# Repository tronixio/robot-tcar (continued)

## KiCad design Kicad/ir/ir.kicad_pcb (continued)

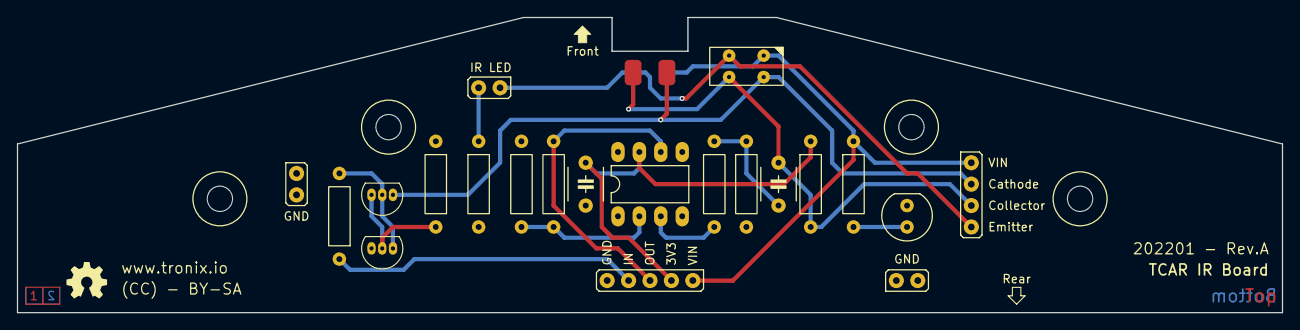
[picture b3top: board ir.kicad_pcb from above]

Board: 2 copper layers, 150.0 x 35.0 mm, 26 parts (1 on the bottom side), 15 nets.

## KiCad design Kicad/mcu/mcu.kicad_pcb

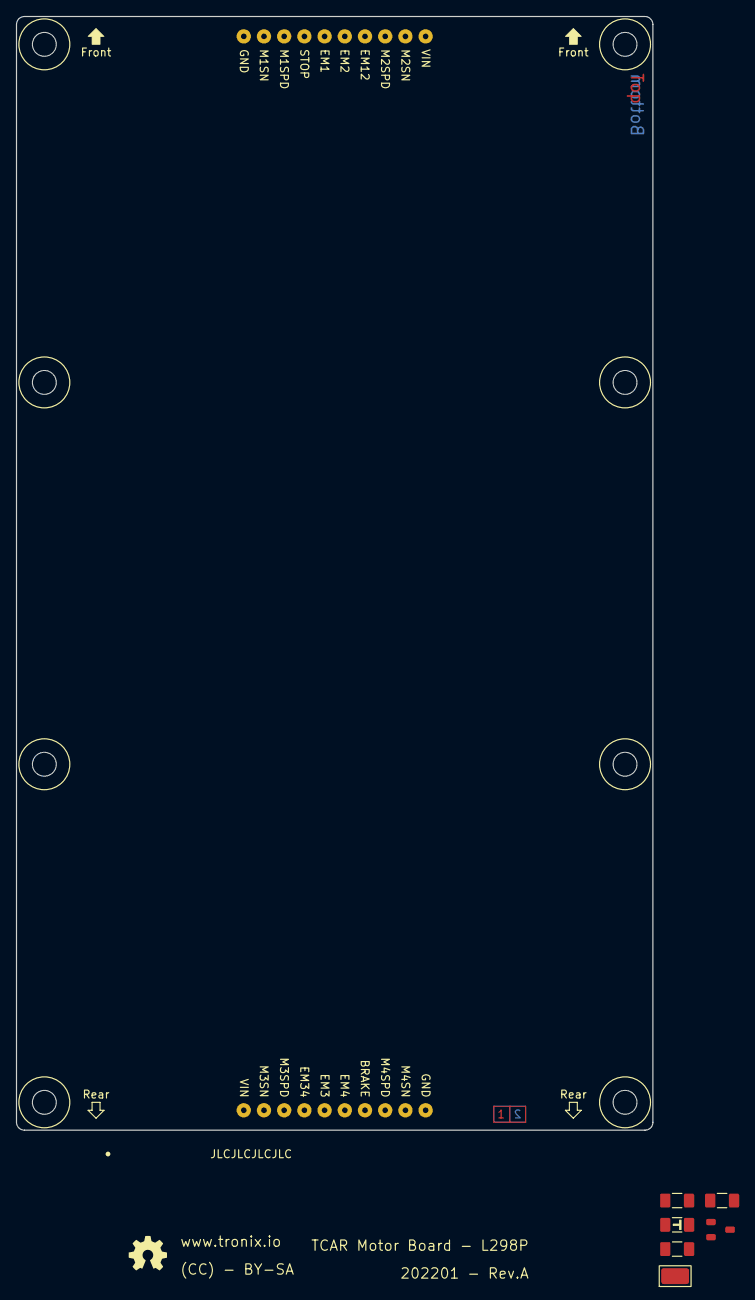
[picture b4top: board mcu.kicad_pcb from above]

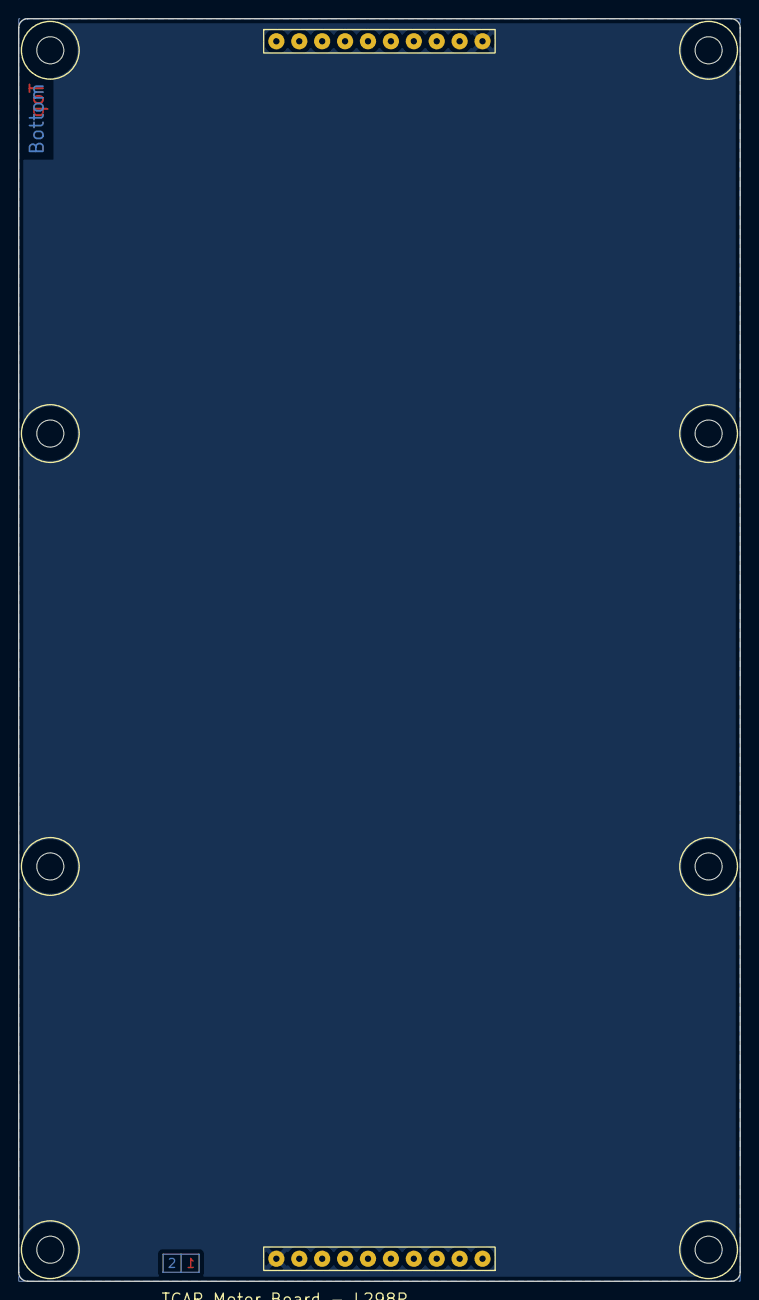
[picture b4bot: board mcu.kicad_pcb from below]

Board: 2 copper layers, 80.0 x 140.0 mm, 16 parts (2 on the bottom side), 4 nets, no tracks yet.

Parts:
C101, C102: 1µ; CAPACITOR-1206
H101, H102, H103, H104, H105, H106, H107, H108: MOUNTING-HOLE-MASK-3MM; M3-MASK
IC101: LM3480-33; SOT-23-3
K301: Front; zzHARWIN-M20-782104x
K302: Rear; zzHARWIN-M20-782104x
LED101: +3V3; LED-1206
R101: 6K8; RESISTOR-1206
TP101: HARWIN-S1751; zzzHARWIN-S1751

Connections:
+3V3: C102.1, IC101.1 (VO), R101.1, TP101.1
GND: C101.2, C102.2, IC101.3 (GND), K301.1, K302.1, LED101.1 (K)
unnamed: LED101.2 (A), R101.2
VIN: C101.1, IC101.2 (VI), K301.10, K302.10

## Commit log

2022-01-23 Update Motor
2022-01-23 Update Motors
2022-03-23 Delete
2022-03-23 Create
2022-03-24 Update MCU
2022-03-24 Create IR
